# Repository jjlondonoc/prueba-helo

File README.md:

# Prueba técnica para Helo

**Autor:** Juan José Londoño - Ingeniero Biomédico M.Sc

**Fecha**: 30/11/2025

## Descripción

En este repo se encuentran las 6 carpetas con las soluciones a las 6 actividades planteadas por la prueba técnica para Helo. Se encuentra en algunas carpetas un README con explicación adicional de lo que hice, los patrones de diseño que apliqué y las prácticas que usé.

El diseño de PCB lo realicé con **kicad**, configurando el entorno y especificaciones de la tarjeta alineado con el fabricante JLCPB, admeás seleccioné los componentes específicos según criterios de diseño como consumo, corrientes, rendimiento, etc. y generé el BOM alineado con JLCPB.

> Quedo atento a cualquier duda sobre las soluciones a las actividades en esta prueba técnica.

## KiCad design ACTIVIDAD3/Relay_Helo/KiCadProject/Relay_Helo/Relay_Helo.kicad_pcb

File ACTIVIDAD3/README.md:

# Diseño de PCB

Diseñé la PCB usando el software **kicad**, implementé constraints y configuré todo el entorno de desarrollo para fabricar la PCB según las especificaciones de **JLCPCB** que es el fabricante que usa Helo. La configuraciones de vías, tracks, clearance, holes, etc. las escogí para que la PCB pueda ser fabricada en el estándar normal, es decir, sin sobrecostos.

También completé el BOM (Bill of Materials) de la tarjeta con los componentes reales a usar incluyendo su link y part number de LCSC que es lo que exigen JLCPCB por si se quisiera hacer el ensamblaje con ellos en china directamente.

Apliqué aislamiento galvánico en la tarjeta para que la parte de potencia AC estuviera aislada de la parte de control  y también creé agujeros de montaje por si son necesarios para la integración de la tarjeta en algún dispositivo.

Usé componentes con encapsulado SMD 0603 en su mayoría pensando en que sean fáciles de soldar a mano por parte de los técnicos y que sean sencillas las posibles reparqciones o reemplazo de componentes.

La serigrafía también la implementé siguiendo patrones de diseño profesionales de PCB.

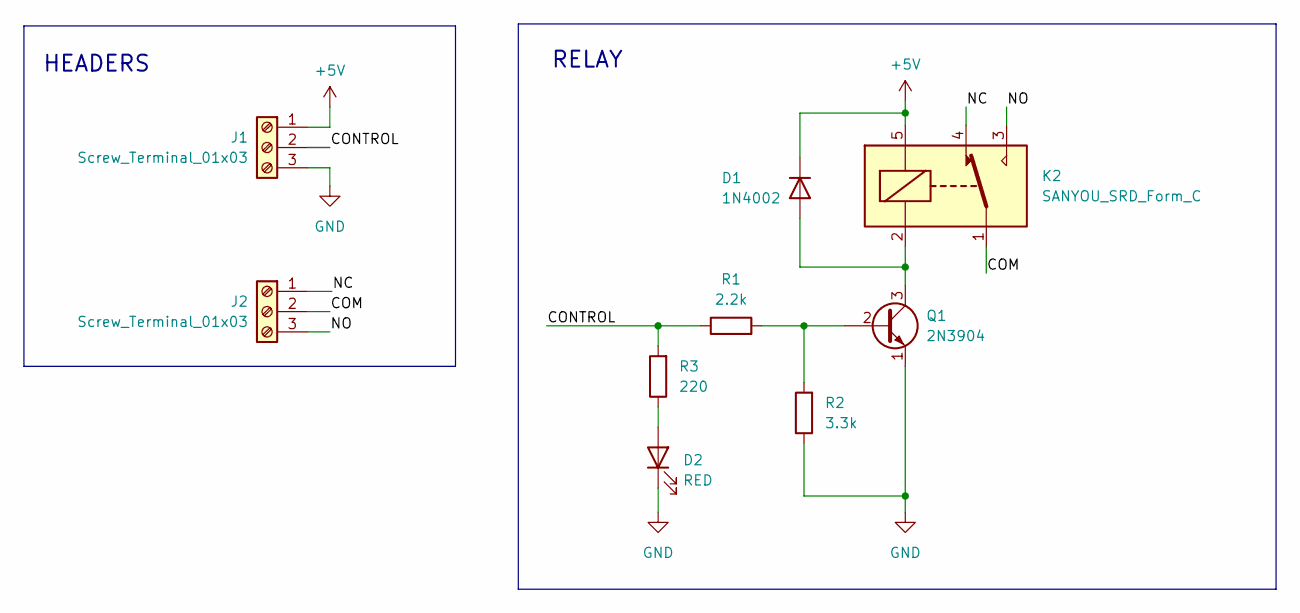
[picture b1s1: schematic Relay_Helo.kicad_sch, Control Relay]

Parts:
D1: 1N4002; D_SOD-123; LCSC PART # C18199086
D2: RED; LED_0603_1608Metric; LCSC PART # C19171390
J1, J2: Screw_Terminal_01x03; TerminalBlock_bornier-3_P5.08mm; LCSC LINK DNP
K2: SANYOU_SRD_Form_C; Relay_SPDT_SANYOU_SRD_Series_Form_C; LCSC PART # C35449
Q1: 2N3904; SOT-23; LCSC PART # C18536
R1: 2.2k; R_0603_1608Metric; LCSC PART # C114662
R2: 3.3k; R_0603_1608Metric; LCSC PART # C108078
R3: 220; R_0603_1608Metric; LCSC PART # C107696

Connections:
+5V: D1.1 (K), J1.1, K2.5
/COM: J2.2, K2.1
/CONTROL: J1.2, R1.1, R3.2
/NC: J2.1, K2.4
/NO: J2.3, K2.3
GND: D2.1 (K), J1.3, Q1.1 (E), R2.1
unnamed: D1.2 (A), K2.2, Q1.3 (C)
unnamed: D2.2 (A), R3.1
unnamed: Q1.2 (B), R1.2, R2.2

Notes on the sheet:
RELAY
HEADERS

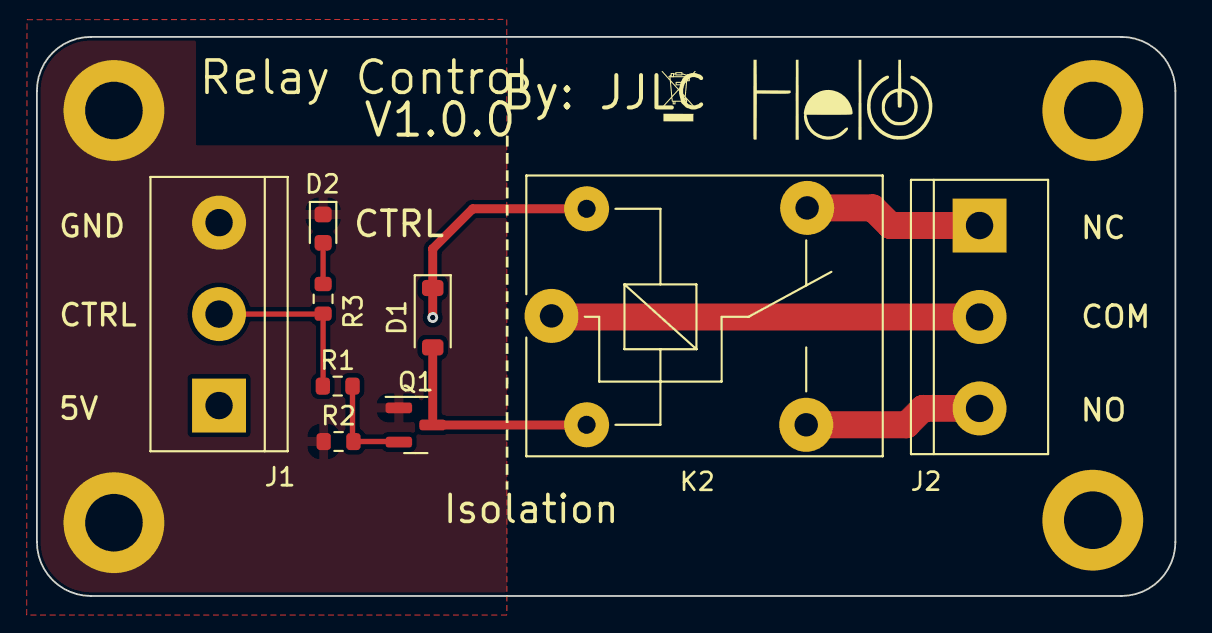
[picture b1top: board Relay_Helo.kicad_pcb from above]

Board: 2 copper layers, 63.2 x 31.1 mm, 9 parts (0 on the bottom side), 9 nets.

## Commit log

2025-12-01 PCB images
2025-12-01 PCB schematic
